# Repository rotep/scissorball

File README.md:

# ScissorBall 36

**A low-profile split keyboard with laptop-style scissor switches and a thumb trackball.**
36 keys · Kailh PG1425 “X-Switch” · 25 mm trackball (PMW3360) under the right thumb · RP2040 · QMK · wired (TRRS)

[日本語 README](README.ja.md) · [Build guide (日本語)](docs/build-guide.ja.md)

> **Status: rev 1.0 – designed, DRC-clean, not yet built.** Everything here is generated and checked in software
> (routing, DRC, 3D interference). No physical prototype exists yet – see [Known risks](#known-risks) before ordering.

## Why

Scissor switches keep the key field thin, but a trackball is inherently tall (sensor stack + ball).
ScissorBall keeps that step small by

- using a **25 mm ball** instead of the usual 34 mm,
- mounting the **sensor level on the case floor**, and
- **tilting only the key PCB** (10° tent toward the thumbs + 5° negative tilt), so the thumb keys rise to meet the ball.

| Height above desk (right half) | |
|---|---|
| Ball top | 36.6 mm |
| Thumb key next to the ball (T1) | 31.6 mm → **5 mm step** |
| Innermost thumb key (T0) | 35.5 mm |
| Lowest corner (pinky top row) | 13.4 mm |

A flat build would put the keys at ~11.5 mm, i.e. a ~25 mm step up to the ball.

## Specs

| | |
|---|---|
| Keys | 5×3 per hand + thumbs (left 3 / right 2) + 1 extra right-pinky key = 36 |
| Pitch / stagger | 18 × 18 mm, column stagger derived from Keyball39 |
| Switch | Kailh PG1425 (needs its dedicated scissor keycaps) |
| MCU | Waveshare RP2040-Zero ×2, mounted flat |
| Split link | TRRS, single-wire half-duplex serial (GP1) |
| Pointing | PMW3360 on the [monkeypad breakout](https://github.com/monkeypad/pmw3360-breakout), 25 mm ball on three Ø2.5 mm ceramic balls |
| Firmware | QMK, one `.uf2` for both halves (handedness pin GP29), auto mouse layer, drag-scroll |
| Case | 3D printed, fits a 256 mm bed (made for Bambu Lab P2S), no supports |

## Repository layout

```
hardware/pcb/left|right   KiCad 9 boards (.kicad_pro/.kicad_pcb) + DRC report + board STEP
hardware/pcb/lib          custom footprints (PG1425, RP2040-Zero, PJ-320A)
hardware/case             case halves + ball bezel (STEP / STL / 3MF)
production                gerber + drill zip per half (JLCPCB-ready)
firmware/scissorball36    QMK keyboard definition + default keymap
firmware/*.uf2            prebuilt firmware
docs                      build guide, 1:1 printable layout & PCB PDFs, images
tools                     generators – everything above is produced from tools/layout.py
```

There is no schematic: the netlist lives in [`tools/pcb.py`](tools/pcb.py) (switch matrix, MCU pin map, TRRS, sensor header) and the boards are placed and routed from it.

| PCB left | PCB right |
|---|---|
|  |  |

## Build it

1. **Order PCBs** – upload `production/scissorball_left_gerber.zip` and `..._right_...zip` separately (2 layers, 1.6 mm). The small rectangular cut-out under every switch is intentional (clearance for the switch’s bottom boss).
2. **Print** `hardware/case/*` – PETG or PLA, 0.2 mm, 3 walls, 15–20 % infill, no supports. Importing the STEP files into Bambu Studio gives the cleanest result.
3. **Flash** `firmware/scissorball36_default.uf2` to both RP2040-Zeros (hold BOOT while plugging in).
4. **Assemble** – see the [build guide](docs/build-guide.ja.md) (BOM, soldering order, sensor mounting).

### Parts (both halves)

| Part | Qty |
|---|---|
| Kailh PG1425 X-Switch with keycaps | 36 |
| Waveshare RP2040-Zero | 2 |
| 1N4148W diode, SOD-123 | 36 |
| PJ-320A TRRS jack + 4-pole cable | 2 + 1 |
| PMW3360 breakout (monkeypad, incl. sensor + LM19-LSI lens) | 1 |
| 25 mm trackball + Ø2.5 mm ceramic balls (Si3N4/ZrO2) | 1 + 3 |
| M2 self-tapping screws (4–6 mm) | 20 |
| Rubber feet ≥ 1.5 mm | 8 |

## Firmware

```sh
cp -r firmware/scissorball36 $QMK_HOME/keyboards/
qmk compile -kb scissorball36 -km default
```

Default keymap: QWERTY base, `NUM` (left inner thumb), `SYM` (right inner thumb), `FN` (right pinky extra key), and an auto-activating `MOUSE` layer (J/K/L = left/middle/right click, H or ; held = scroll). The sensor looks *up* at the ball, so axis orientation may need flipping – adjust `POINTING_DEVICE_ROTATION_*` / `POINTING_DEVICE_INVERT_*` in [`config.h`](firmware/scissorball36/config.h).

## Regenerating the design

Edit [`tools/layout.py`](tools/layout.py) (pitch, stagger, ball position, `TENT_DEG`, `TILT_DEG`) and run:

```sh
make all KICAD_PY=<python with pcbnew> FREECAD_PY=<python with FreeCAD> FREEROUTING=/path/to/freerouting.jar
```

`make pcb-left` places parts, autoroutes with Freerouting, closes any leftover connections with a small A* router (`tools/fixroute.py`) and runs DRC. `make check` verifies the case against the PCB, key caps (at rest and pressed), MCU, jack, sensor board and ball, and renders the previews.
Toolchain used: KiCad 9.0, FreeCAD 1.0, Freerouting 2.0, QMK 0.34.

## Known risks

- **PG1425 footprint** is re-drawn from community footprints ([moduloindustries](https://github.com/moduloindustries/libmodulo), [shikamiya](https://github.com/shikamiya/kicad-footprint-kailh-pg1425-x-switch)) and checked against modulo’s STEP model, but not against a physical switch. Print `docs/pcb_*_1to1.pdf` at 100 % and test-fit a switch first.
- **Lens-to-ball distance** (7.2 mm from the breakout’s lens-side face) is taken from a PMW3360 + LM19-LSI assembly model. If tracking is poor, shim or sand the four datum posts, or tune `PMW33XX_LIFTOFF_DISTANCE`.
- **Switch availability** – PG1425 is niche and often sold “while stocks last”. Secure switches before ordering boards.
- The TRRS line carries 5 V: never plug/unplug it while USB is connected.

## Credits

- Footprint geometry: [moduloindustries/libmodulo](https://github.com/moduloindustries/libmodulo) (GPL-3.0), [shikamiya/kicad-footprint-kailh-pg1425-x-switch](https://github.com/shikamiya/kicad-footprint-kailh-pg1425-x-switch) (MIT), [bobu01/RP2040-Zero-Kicad-Footprint-1mm](https://github.com/bobu01/RP2040-Zero-Kicad-Footprint-1mm) (GPL-3.0), [keebio/Keebio-Parts.pretty](https://github.com/keebio/Keebio-Parts.pretty) (MIT, PJ-320A)
- Layout proportions inspired by [Keyball](https://github.com/Yowkees/keyball); sensor board by [monkeypad](https://github.com/monkeypad/pmw3360-breakout)
- [QMK](https://qmk.fm), [KiCad](https://www.kicad.org), [FreeCAD](https://www.freecad.org), [Freerouting](https://github.com/freerouting/freerouting)

## License

Hardware, case and tools: **GPL-3.0-or-later** (see [LICENSE](LICENSE); footprints derive from GPL-3.0 sources).
Firmware (`firmware/`): **GPL-2.0-or-later**, as part of QMK.

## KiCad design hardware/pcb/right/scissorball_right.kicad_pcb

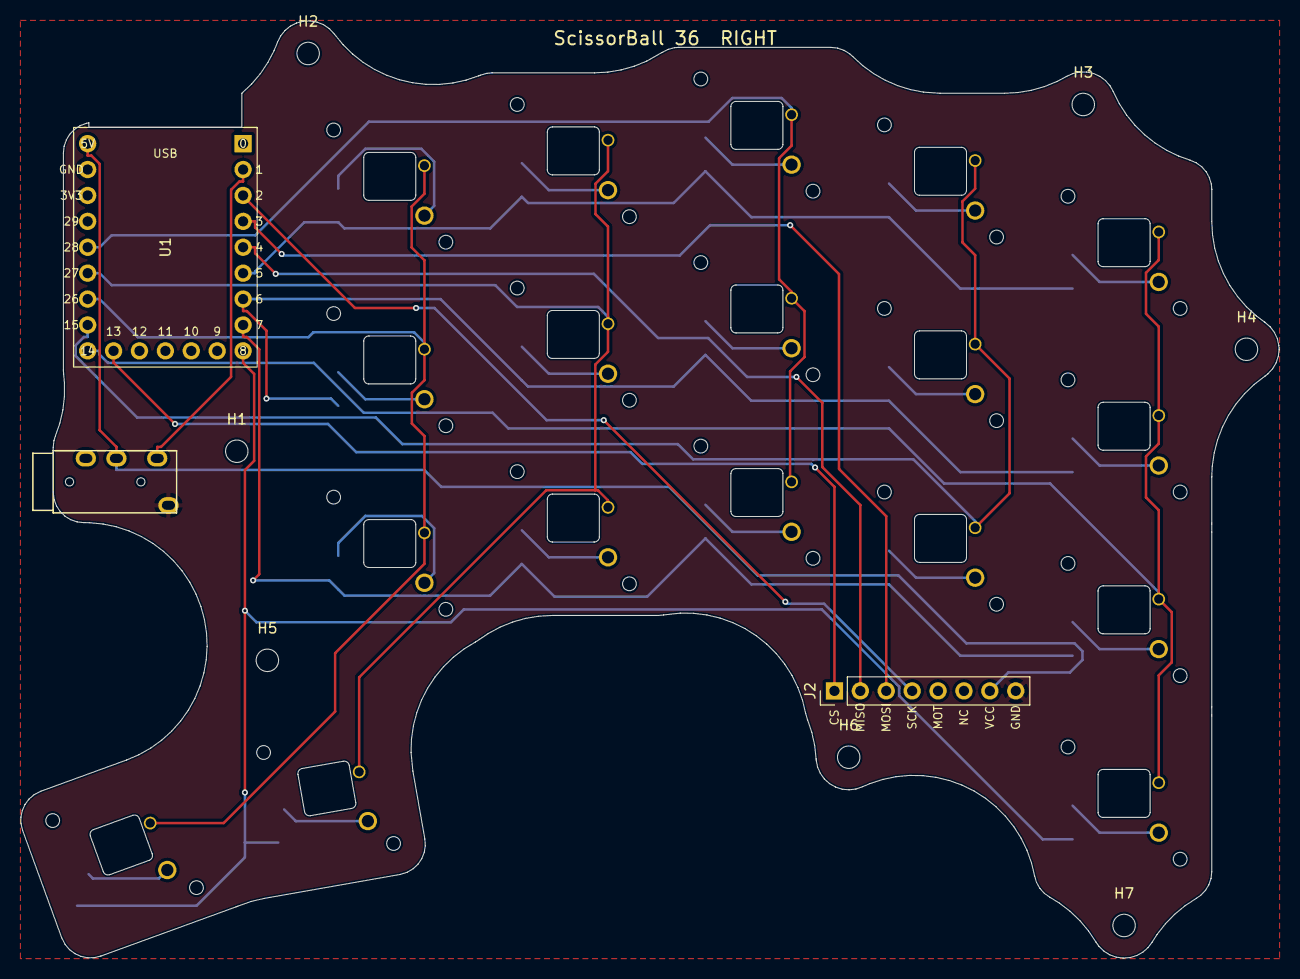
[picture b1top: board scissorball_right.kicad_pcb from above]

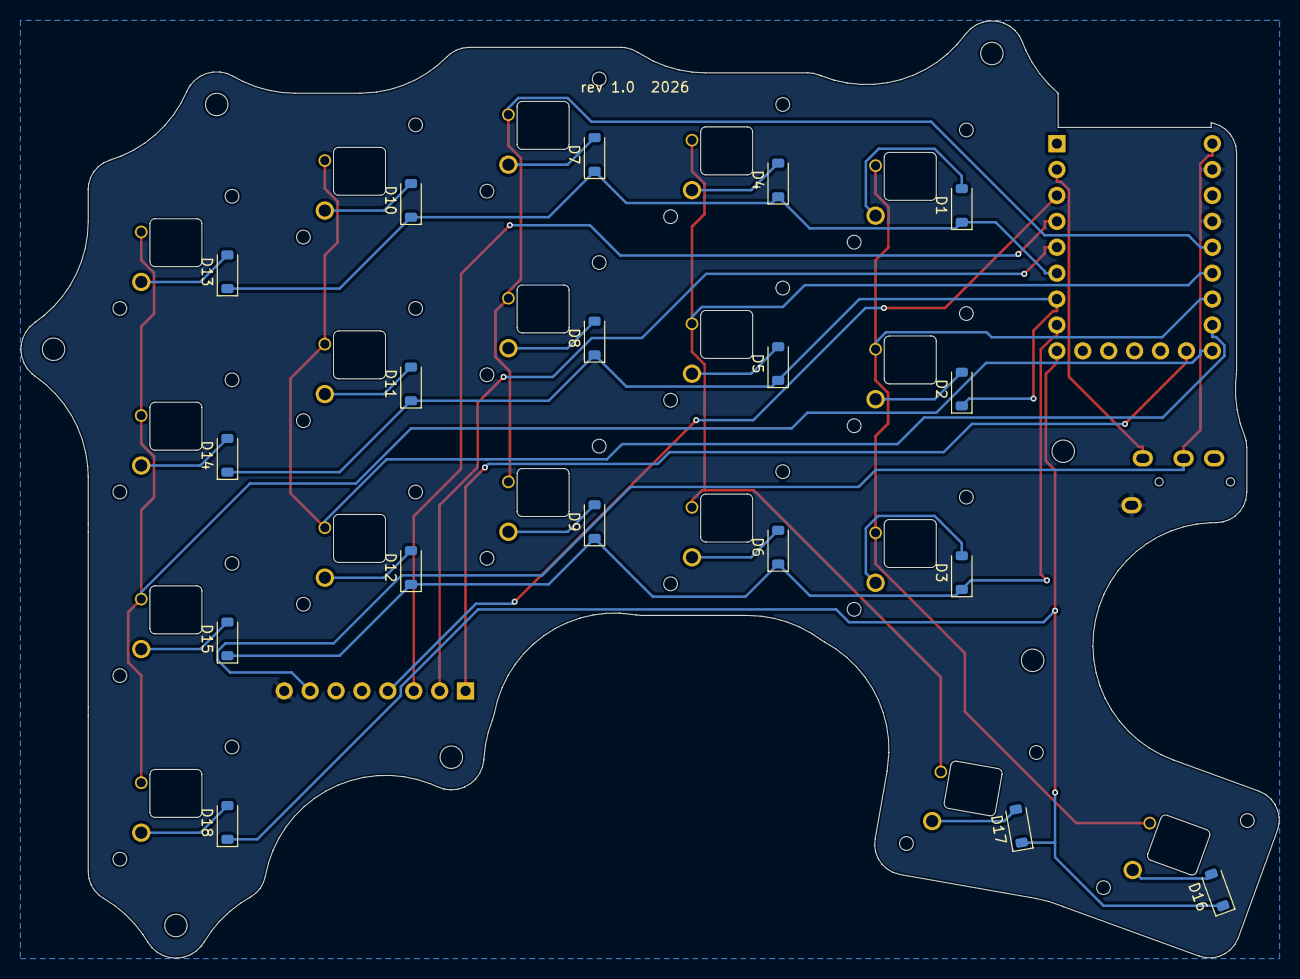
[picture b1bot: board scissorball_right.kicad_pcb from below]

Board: 2 copper layers, 123.4 x 91.9 mm, 46 parts (18 on the bottom side), 34 nets.

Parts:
D1, D2, D3, D4, D5, D6, D7, D8, D9, D10, D11, D12, D13, D14, D15, D16, D17, D18: 1N4148W; D_SOD-123
H1, H2, H3, H4, H5, H6, H7: MountingHole_2.2mm_M2
J1: PJ-320A; SB_TRRS_PJ-320A
J2: PMW3360 breakout; PinHeader_1x08_P2.54mm_Vertical
SW1: K00; SB_Kailh_PG1425
SW2: K10; SB_Kailh_PG1425
SW3: K20; SB_Kailh_PG1425
SW4: K01; SB_Kailh_PG1425
SW5: K11; SB_Kailh_PG1425
SW6: K21; SB_Kailh_PG1425
SW7: K02; SB_Kailh_PG1425
SW8: K12; SB_Kailh_PG1425
SW9: K22; SB_Kailh_PG1425
SW10: K03; SB_Kailh_PG1425
SW11: K13; SB_Kailh_PG1425
SW12: K23; SB_Kailh_PG1425
SW13: K04; SB_Kailh_PG1425
SW14: K14; SB_Kailh_PG1425
SW15: K24; SB_Kailh_PG1425
SW16: T0; SB_Kailh_PG1425
SW17: T1; SB_Kailh_PG1425
SW18: P4; SB_Kailh_PG1425
U1: RP2040-Zero; SB_RP2040_Zero

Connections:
COL0: SW1.1, SW2.1, SW3.1, SW16.1, U1.GP26
COL1: SW4.1, SW5.1, SW6.1, SW17.1, U1.GP27
COL2: SW7.1, SW8.1, SW9.1, U1.GP28
COL3: SW10.1, SW11.1, SW12.1, U1.GP15
COL4: SW13.1, SW14.1, SW15.1, SW18.1, U1.GP14
CS: J2.1, U1.GP13
D1: D1.2, SW1.2
D2: D2.2, SW2.2
D3: D3.2, SW3.2
D4: D4.2, SW4.2
D5: D5.2, SW5.2
D6: D6.2, SW6.2
D7: D7.2, SW7.2
D8: D8.2, SW8.2
D9: D9.2, SW9.2
D10: D10.2, SW10.2
D11: D11.2, SW11.2
D12: D12.2, SW12.2
D13: D13.2, SW13.2
D14: D14.2, SW14.2
D15: D15.2, SW15.2
D16: D16.2, SW16.2
D17: D17.2, SW17.2
D18: D18.2, SW18.2
DATA: J1.2, U1.GP1
GND: J1.1, J2.8, U1.GND, U1.GP29
MISO: J2.2, U1.GP4
MOSI: J2.3, U1.GP3
ROW0: D1.1, D4.1, D7.1, D10.1, D13.1, U1.GP5
ROW1: D2.1, D5.1, D8.1, D11.1, D14.1, U1.GP6
ROW2: D3.1, D6.1, D9.1, D12.1, D15.1, U1.GP7
ROW3: D16.1, D17.1, D18.1, U1.GP8
SCK: J2.4, U1.GP2
VBUS: J1.3, J2.7, U1.5V
